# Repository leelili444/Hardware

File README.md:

# MX_IMU Hardware Design (using KiCad 9)

This repository contains the MX_IMU V1.0 hardware design files, libraries, and production outputs created with KiCad.

## Overview

- Project: MX_IMU (IMU sensor module)
- Tool: KiCad (schematic capture and PCB layout)

## Key Files

- `MX_IMU.kicad_pro` - Project file
- `MX_IMU.kicad_sch` — Main schematic
- `MX_IMU.kicad_pcb` — PCB layout file
- `*.kicad_sym` — Symbol files, located in `library/symbols`
- `*.kicad_mod` (footprints) — Footprint libraries, located in `library/footprints`
- `3DModels/` — Component 3D STEP models for the PCB 3D viewer
- `production/` — Manufacturing outputs (BOM, placement files, IPC netlist, etc.)

## How to Open

1. Install KiCad on your computer (stable or LTS versions recommended).
2. Open the project via `File -> Open Project` and select `MX_IMU.kicad_pro`, or open `MX_IMU.kicad_sch` / `MX_IMU.kicad_pcb` directly.

## Libraries and 3D Models

- Custom symbols: `library/symbols`.
- Custom footprints: `library/footprints` (contained in `.pretty` directories).
- 3D STEP files: `library/3DModels` for the PCB 3D viewer and manufacturing visualization.

## Production Directory

The `production/` directory includes `bom.csv`, `positions.csv` (placement), `netlist.ipc`, and similar files that can be used for ordering or manufacturing.
## License

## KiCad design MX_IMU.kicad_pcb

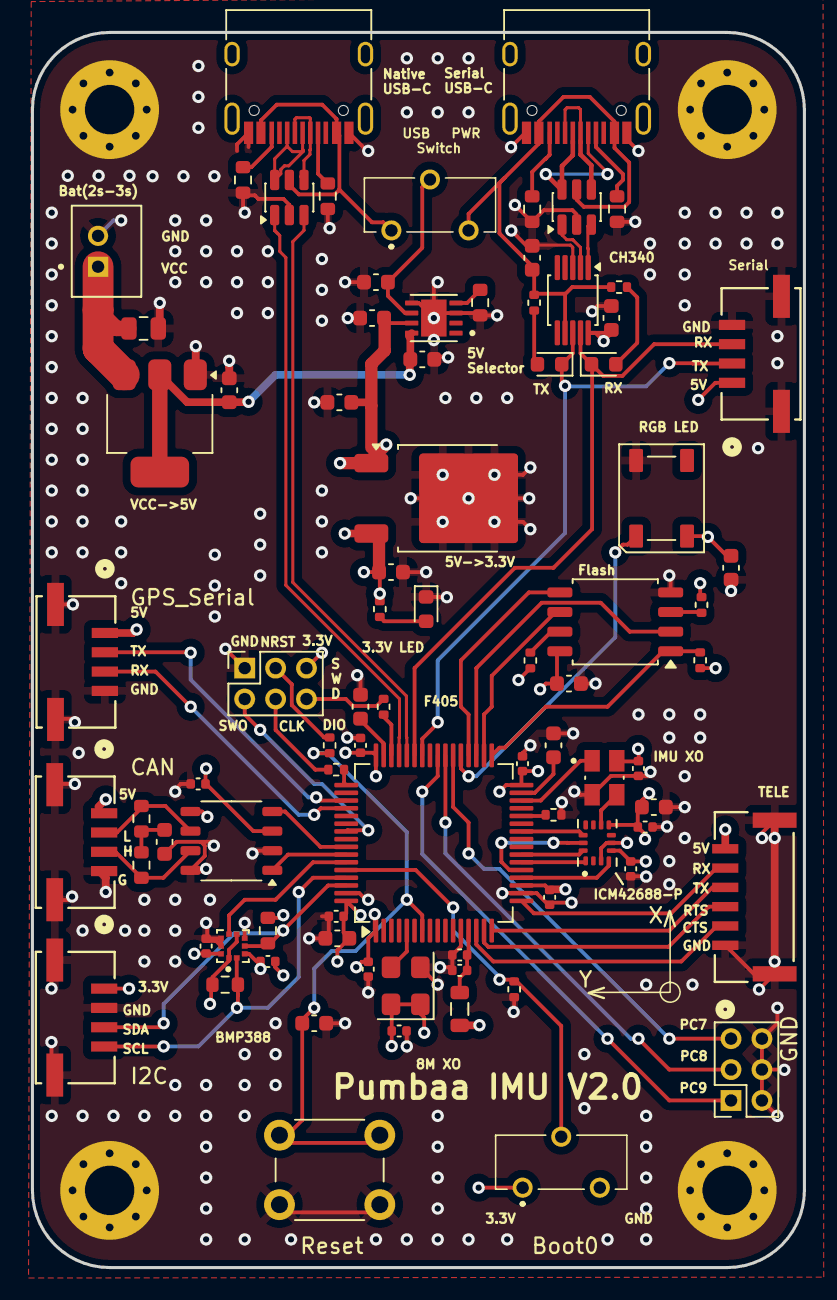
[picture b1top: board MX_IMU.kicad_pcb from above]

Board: 4 copper layers, 50.0 x 80.0 mm, 86 parts (0 on the bottom side), 70 nets.

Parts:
C1, C3, C4, C5, C21, C22, C24: 100nf; C_0603_1608Metric
C2: 10uf/30v; C_0805_2012Metric
C6, C9: 10uf; C_0603_1608Metric
C7: 1u; C_0603_1608Metric
C8, C11, C13, C26: 2u2; C_0603_1608Metric
C10: 4u7; C_0603_1608Metric
C12, C14, C15, C16, C17, C20, C28, C29, C30: 100n; C_0402_1005Metric
C18: 1u; C_0402_1005Metric
C19, C27: 10n; C_0402_1005Metric
C23: 0.01u; C_0402_1005Metric
C25: 0.1u; C_0402_1005Metric
C31: 4n7; C_0603_1608Metric
CAN1: SM04B-GHS-TB(LF)(SN); CONN_SM04B-GHS-TB_JST
D1, D2, D3: LED; LED_0603_1608Metric
FB1: 600 @ 600 MHz; L_0805_2012Metric
GPS_Serial1: SM04B-GHS-TB(LF)(SN); CONN_SM04B-GHS-TB_JST
H1, H2, H3, H4: MountingHole_Pad; MountingHole_3.2mm_M3_Pad_Via
J1: B2B-PH-K-S; JST_B2B-PH-K-S
J2, J3: Native USB; USB_C_Receptacle_HRO_TYPE-C-31-M-12
J4: SM04B-GHS-TB(LF)(SN); CONN_SM04B-GHS-TB_JST
J5, J6: Conn_02x03_Odd_Even; PinSocket_2x03_P2.00mm_Vertical
LSE1: ASEK-32.768KHZ-L-R-T; XTAL_ASEK-32.768KHZ-L-R-T
MainLED1: WS2812B-2020; LED_WS2812B_PLCC4_5.0x5.0mm_P3.2mm
R1, R2, R3: 330R; R_0402_1005Metric
R4: 390R; R_0603_1608Metric
R5, R6, R7, R8: 5.1k; R_0603_1608Metric
R9, R10, R11, R12, R13: 10k; R_0402_1005Metric
R14, R15: 4.7k; R_0603_1608Metric
R16, R17, R18: 22; R_0402_1005Metric
R19, R20: 60R; R_0603_1608Metric
Reset1: SW_Push; SW_PUSH_6mm_H5mm
SW1, SW2: SSSS213000
Serial1: SM04B-GHS-TB(LF)(SN); CONN_SM04B-GHS-TB_JST
TELE1: SM06B-GHS-TB(LF)(SN); CONN_SM06B-GHS-TB_JST
U1: CH340E; MSOP-10_3x3mm_P0.5mm
U2: NCP1117ST50T3G; SOT-223-3_TabPin2
U3: TPS2115ADRBR; SON65P300X300X100-9N
U4: ld39150dt33-r; to-252-2_dpak-2-leg
U5, U6: USBLC6-2SC6; SOT-23-6
U7: STM32F405RGTx; LQFP-64_10x10mm_P0.5mm
U8: X1G0059610004; Oscillator_SMD_SeikoEpson_SG3225CAN-4Pin_3.2x2.5mm
U9: W25Q128JVSIQ; SOIC-8_5.3x5.3mm_P1.27mm
U10: ICM-42688-P; ICM42688p
U11: BMP388
U12: TJA1051T/3; sot96-1_soic-8

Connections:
+3.3V: C1.1, C8.1, C10.1, C12.1, C14.1, C15.1, C16.1, C17.1, C20.1, C23.1, C24.1, C25.1, C26.1, C27.1, C28.2, C29.1, FB1.2, J4.1, J5.5, LSE1.4 (VDD), R1.1, R11.2, R12.2, R13.1, R14.2, R15.2, SW2.1 (NO), U1.10 (V3), U4.3 (VO), U7.1 (VBAT), U7.19 (VDD), U7.32 (VDD), U7.48 (VDD), U7.64 (VDD), U8.1 (ST#), U8.4 (Vcc), U9.8 (VCC), U10.5 (VDDIO), U10.8 (VDD), U11.1 (VDDIO), U11.6 (CSB), U11.10 (VDD), U12.5 (V_{IO})
+3.3VA: C18.1, C19.1, FB1.1, U7.13 (VDDA)
+5V: C7.1, C9.1, C22.1, C30.1, CAN1.1, GPS_Serial1.1, MainLED1.4 (VDD), Serial1.1, TELE1.6, U3.7 (OUT), U4.1 (VI), U12.3 (V_{CC})
+5VD: C4.1, C6.1, U2.2 (VO), U3.8 (IN1)
/Connectors/CANH: CAN1.3, R20.1, U12.7 (CANH)
/Connectors/CANL: CAN1.2, R19.1, U12.6 (CANL)
BOOT0: R9.1, SW2.2 (C), U7.60 (BOOT0)
BOOT1: R10.1, U7.28 (PB2)
Baro_INT: U7.59 (PB7), U11.7 (INT)
Baro_SCL: J4.4, R14.1, U7.61 (PB8), U11.2 (SCK)
Baro_SDA: J4.3, R15.1, U7.62 (PB9), U11.4 (SDI)
CAN2_RX: U7.57 (PB5), U12.4 (RXD)
CAN2_TX: U7.58 (PB6), U12.1 (TXD)
C_Native_D+: J2.A6 (D+), J2.B6 (D+), U5.6 (I/O1)
C_Native_D-: J2.A7 (D-), J2.B7 (D-), U5.4 (I/O2)
C_Serial_D+: J3.A6 (D+), J3.B6 (D+), U6.4 (I/O2)
C_Serial_D-: J3.A7 (D-), J3.B7 (D-), U6.6 (I/O1)
Flash_CS: R13.2, U7.33 (PB12), U9.1 (~CS)
Flash_MISO: U7.35 (PB14), U9.2 (DO/IO_{1})
Flash_MOSI: U7.36 (PB15), U9.5 (DI/IO_{0})
Flash_SCK: U7.34 (PB13), U9.6 (CLK)
GND: C1.2, C2.2, C3.2, C4.2, C5.2, C6.2, C7.2, C8.2, C9.2, C10.2, C11.2, C12.2, C13.2, C14.2, C15.2, C16.2, C17.2, C18.2, C19.2, C20.2, C21.1, C22.2, C23.2, C24.2, C25.2, C26.2, C27.2, C28.1, C29.2, C30.2, C31.2, CAN1.4, CAN1.5, CAN1.6, D1.1 (K), GPS_Serial1.4, GPS_Serial1.5, GPS_Serial1.6, H1.1, H2.1, H3.1, H4.1, J1.2, J2.A1 (GND), J2.A12 (GND), J2.B1 (GND), J2.B12 (GND), J3.A1 (GND), J3.A12 (GND), J3.B1 (GND), J3.B12 (GND), J4.2, J4.5, J4.6, J5.1, J6.2, J6.4, J6.6, LSE1.2 (GND/CASE), MainLED1.2 (VSS), R4.1, R5.2, R6.1, R7.2, R8.1, R9.2, R10.2, Reset1.2, Serial1.4, Serial1.5, Serial1.6, TELE1.1, TELE1.7, TELE1.8, U1.3 (GND), U2.1 (GND), U3.3 (D1), U3.5 (GND), U3.9 (EPAD), U4.2 (GND), U5.2 (GND), U6.2 (GND), U7.12 (VSSA), U7.18 (VSS), U7.63 (VSS), U8.2 (GND), U9.4 (GND), U10.3 (RESV_3), U10.6 (GND), U11.3 (VSS), U11.5 (SDO), U11.8 (VSS__1), U11.9 (VSS__2), U12.2 (GND), U12.8 (S)
GPS_RX: GPS_Serial1.3, U7.52 (PC11)
GPS_TX: GPS_Serial1.2, U7.51 (PC10)
GYRO_CS: U7.26 (PB0), U10.12 (AP_CS)
GYRO_INT1: U7.20 (PA4), U10.4 (INT1/INT)
GYRO_LSE: LSE1.1 (TRI-STATE), U7.30 (PB11)
GYRO_MISO: U7.22 (PA6), U10.1 (AP_SDO/AP_AD0)
GYRO_MOSI: U7.23 (PA7), U10.14 (AP_SDA/AP_SDIO/AP_SDI)
GYRO_SCK: U7.21 (PA5), U10.13 (AP_SCL/AP_SCLK)
HSE_IN: U7.5 (PH0), U8.3 (OUT)
NRST: C21.2, R16.1, Reset1.1, U7.7 (NRST)
Native_D+: U5.1 (I/O1), U7.45 (PA12)
Native_D-: U5.3 (I/O2), U7.44 (PA11)
Native_VBUS: J2.A4 (VBUS), J2.A9 (VBUS), J2.B4 (VBUS), J2.B9 (VBUS), SW1.1 (NO), U5.5 (VBUS)
unnamed: C31.1, R19.2, R20.2
unnamed: D1.2 (A), R1.2
unnamed: D2.2 (A), R2.2
unnamed: D3.2 (A), R3.2
unnamed: J2.A5 (CC1), R5.1
unnamed: J2.B5 (CC2), R6.2
unnamed: J3.A5 (CC1), R7.1
unnamed: J3.B5 (CC2), R8.2
unnamed: J5.3, R16.2
unnamed: J5.4, R17.2
unnamed: J5.6, R18.2
unnamed: LSE1.3 (OUTPUT), U10.9 (INT2/FSYNC/CLKIN)
unnamed: R4.2, U3.4 (ILIM)
unnamed: C11.1, U7.31 (VCAP_1)
unnamed: C13.1, U7.47 (VCAP_2)
unnamed: R12.1, U9.7 (~HOLD/~RESET/IO_{3})
unnamed: R11.1, U9.3 (~WP/IO_{2})
SWCLK: R17.1, U7.49 (PA14)
SWDIO: R18.1, U7.46 (PA13)
SWO: J5.2, U7.55 (PB3)
Serial_D+: U1.1 (UD+), U6.3 (I/O2)
Serial_D-: U1.2 (UD-), U6.1 (I/O1)
Serial_RX: D3.1 (K), Serial1.3, U1.9 (RXD), U7.43 (PA10)
Serial_TX: D2.1 (K), Serial1.2, U1.8 (TXD), U7.42 (PA9)
Serial_VBUS: C5.1, J3.A4 (VBUS), J3.A9 (VBUS), J3.B4 (VBUS), J3.B9 (VBUS), R2.1, R3.1, SW1.3 (NC), U1.7 (VCC), U6.5 (VBUS)
Status_LED: MainLED1.3 (DIN), U7.37 (PC6)
TELE_CTS: TELE1.2, U7.14 (PA0)
TELE_RTS: TELE1.3, U7.15 (PA1)
TELE_RX: TELE1.5, U7.17 (PA3)
TELE_TX: TELE1.4, U7.16 (PA2)
Tim8_2: J6.5, U7.38 (PC7)
Tim8_3: J6.3, U7.39 (PC8)
Tim8_4: J6.1, U7.40 (PC9)
VBUS: C3.1, SW1.2 (C), U3.6 (IN2)
VCC: C2.1, J1.1, U2.3 (VI)

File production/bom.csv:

Designator,Footprint,Quantity,Value,LCSC Part #
"C1, C21, C22, C24, C3, C4, C5",0603,7,100nf,
C10,0603,1,4u7,C19666
"C11, C13, C26, C8",0603,4,2u2,C23630
"C12, C14, C15, C16, C17, C20, C30",0402,7,100n,C1525
C18,0402,1,1u,C52923
C19,0402,1,10n,C15195
C2,0805,1,10uf/30v,
C23,0402,1,0.01u,
C25,0402,1,0.1u,
C27,0402,1,10n,
"C28, C29",0201,2,100n,
C31,0603,1,4n7,
"C6, C9",0603,2,10uf,
C7,0603,1,1u,
"CAN1, GPS_SERIAL1, J4, SERIAL1",CONN_SM04B-GHS-TB_JST,4,SM04B-GHS-TB,
"D1, D2, D3",0603,3,LED,
FB1,0805,1,600 @ 600 MHz,C1017
"H1, H2, H3, H4",MountingHole_3.2mm_M3_Pad_Via,4,MountingHole_Pad,
J1,JST_B2B-PH-K-S,1,B2B-PH-K-S,
"J2, J3",USB_C_Receptacle_HRO_TYPE-C-31-M-12,2,Native USB,
"J5, J6",PinSocket_2x03_P2.00mm_Vertical,2,Conn_02x03_Odd_Even,
LSE1,XTAL_ASEK-32.768KHZ-L-R-T,1,ASEK-32.768KHZ-L-R-T,
MAINLED1,LED_WS2812B-2020_PLCC4_2.0x2.0mm,1,WS2812B-2020,C965555
R1,0402,1,330R,C25744
"R10, R11, R12, R13",0402,4,10k,C25744
"R14, R15",0603,2,4.7k,
"R16, R17, R18",0402,3,22,C25092
"R19, R20",0603,2,60R,C166918
"R2, R3",0402,2,330,C25744
R4,0603,1,390R,
"R5, R6, R7, R8",0603,4,5.1k,
R9,0603,1,10k,
RESET1,SW_PUSH_6mm_H5mm,1,SW_Push,C455109 
"SW1, SW2",SSSS213000,2,SSSS213000,
TELE1,CONN_SM06B-GHS-TB_JST,1,SM06B-GHS-TB,
U1,MSOP-10_3x3mm_P0.5mm,1,CH340E,
U10,ICM42688p,1,ICM-42688-P,
U11,BMP388,1,BMP388, #  C779278 
U12,sot96-1_soic-8,1,TJA1051T/3,
U2,SOT-223-3_TabPin2,1,NCP1117-5.0_SOT223,
U3,SON65P300X300X100-9N,1,TPS2115ADRBR,
U4,to-252-2_dpak-2-leg,1,ld39150dt33-r,
"U5, U6",SOT-23-6,2,USBLC6-2SC6,
U7,LQFP-64_10x10mm_P0.5mm,1,STM32F405RGTx,C15742
U8,Oscillator_SMD_SeikoEpson_SG3225CAN-4Pin_3.2x2.5mm,1,"8Mhz,50ppm",X1G0059610004 
U9,SOIC-8_5.3x5.3mm_P1.27mm,1,W25Q128JVSIQ,

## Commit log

2025-10-20 update pcb
2025-10-21 save
2025-10-23 update spi flash and ws2812b
2025-10-23 update library
2025-10-23 clean files
2025-10-26 update value for capacity and resistor
2025-10-26 update pcb and imu 3d model
2025-10-28 updateu
2025-11-04 beta
2025-11-10 update V2_RC1
2025-11-12 update spi flash
2025-11-17 update for production
2025-11-18 PumbaaV2_RC2
2026-01-04 compact IMU module for integration
2026-01-04 IMU_IMU V1.0 is ready.
    correct ch340e
2026-01-04 clean up
2026-04-11 add liscenes
2026-04-11 Fix capitalization of 'License' section in README
